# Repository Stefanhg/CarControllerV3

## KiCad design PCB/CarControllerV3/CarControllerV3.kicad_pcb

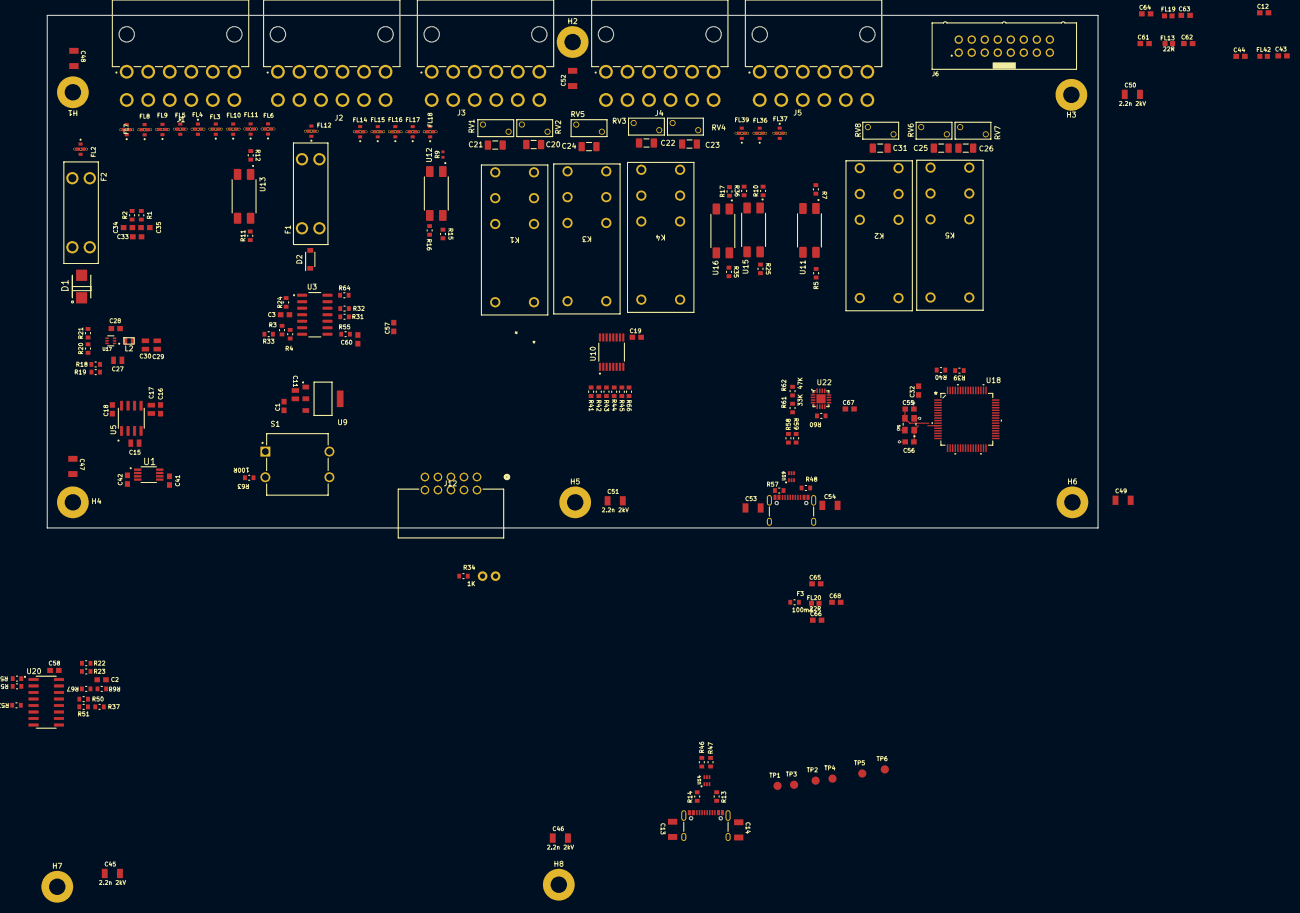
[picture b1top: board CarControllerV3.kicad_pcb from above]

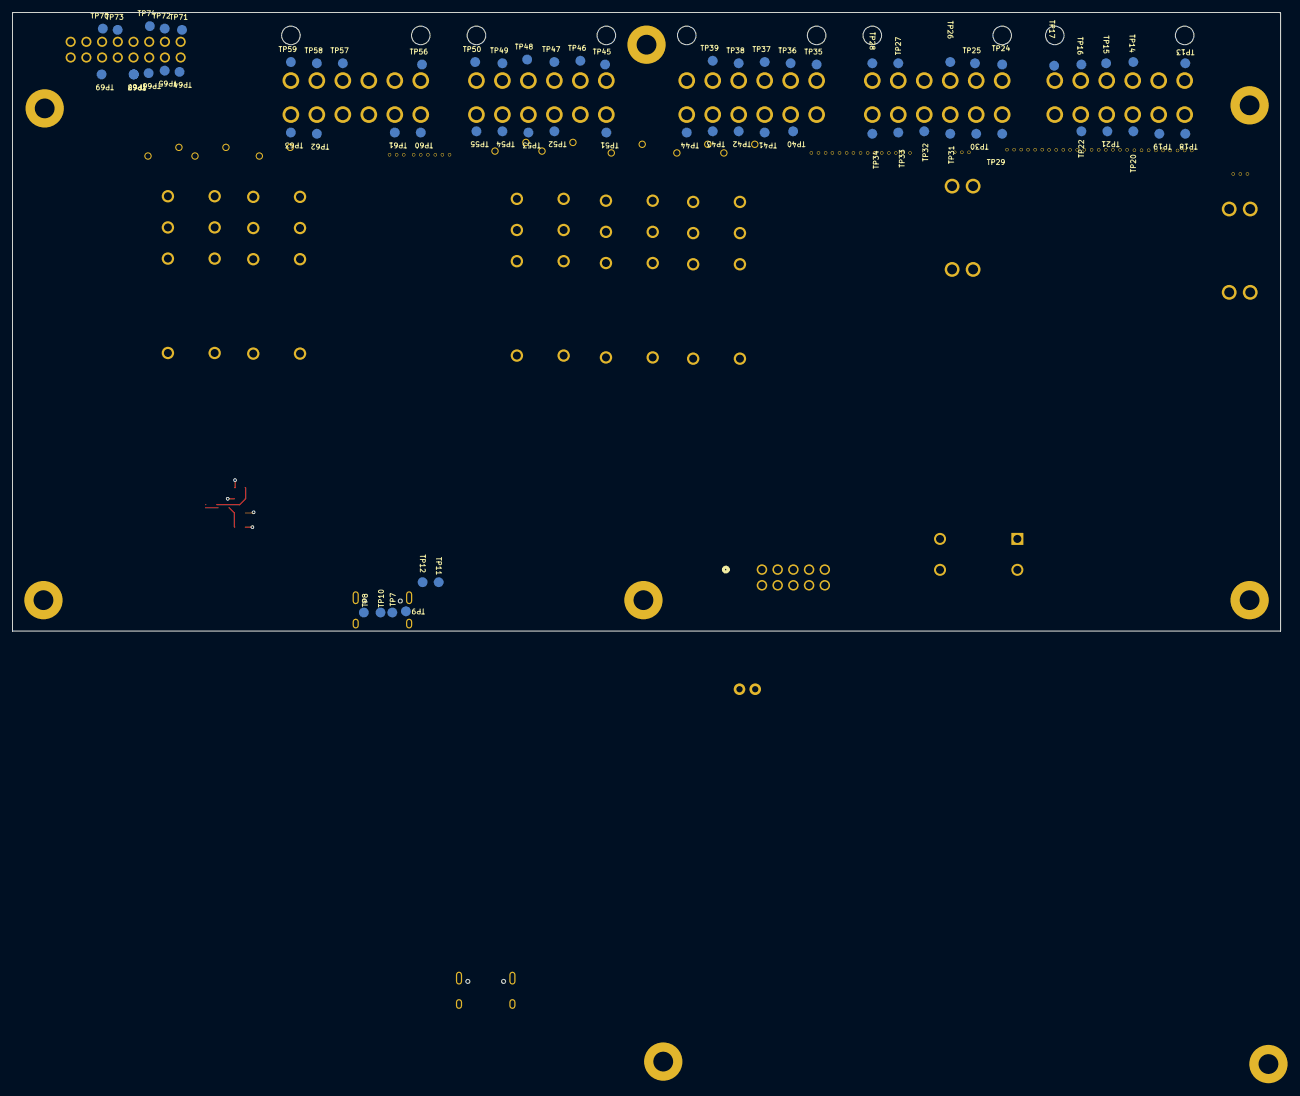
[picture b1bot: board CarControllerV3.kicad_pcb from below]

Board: 2 copper layers, 205.0 x 100.0 mm, 263 parts (67 on the bottom side), 171 nets.

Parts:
C1, C2, C3, C12, C16, C18, C19, C28, C32, C41, C42, C57, C58, C65, C66, C67: 100n; CAPC1608X90
C11, C15, C17, C27, C29, C30: 10uF; CC0805KKX5R8BB106-CAPC2013X145N
C13, C14, C45, C46, C47, C48, C49, C50, C51, C52, C53, C54: 2.2n 2kV; C1206X222KGRACTU-CAP3216X125N
C20, C21, C22, C23, C24, C25, C26, C31: 100n; CAPC3216X180N
C33, C34, C35, C60: 100p; CAPC1608X90
C43, C44, C61, C62, C63, C64: 10n; CAPC1608X90
C55, C56: 12p; CAPC1608X90
C68: 1uF; CAPC1608X90
D1: SS54B; SS54B-DIOM4336X244N
D2: 1N4007W-T; SODFL3818X130N
F1, F2: 3557-2; FUSE_3557-2
F3: 100mA; FEMTOSMDC010F-2-RESC1608X60N
FL2, FL3, FL4, FL5, FL6, FL7, FL8, FL9, FL10, FL11, FL12, FL14, FL15, FL16, FL17, FL18, FL36, FL37, FL39: 22nF; FIL_NFM21CC223R1H3D
FL13, FL19, FL20, FL42: 22R; BLM18BA220SN1D-BEADC1608X95N
H1, H2, H3, H4, H5, H6, H7, H8: 3.2mm; 3.2mm_plated
J1, J2, J3, J4, J5: 649012227222
J6: 61201621621
J9, J11: USB_C_Receptacle; USB-C_16
J10: Conn_01x02; 1x02
J12: 702471052; CONN_7024710XX_MOL
K1, K2, K3, K4, K5: RT424005; RELAY-SPDT_5mm
L2: 4.7uH; CC0805
R1, R2, R3, R4, R5, R11, R23, R25, R31, R32, R33, R35, R60, R67: 10K; RC0603FR-RESC1608X60N
R7, R12: 22K; RC0603FR-RESC1608X60N.pretty
R9: 1K; RC0402FR-RESC1005X40N
R10, R17: 2.7K; RC0603FR-RESC1608X60N.pretty
R13, R14, R48, R57: 5.1K; RC0603FR-RESC1608X60N.pretty
R15, R16, R55, R63, R64: 100R; RC0603FR-RESC1608X60N.pretty
R18, R21: 7.5K; RC0603FR-RESC1608X60N.pretty
R19, R20: 39K; RC0603FR-RESC1608X60N.pretty
R22: 390K; RC0603FR-RESC1608X60N.pretty
R24, R34, R37, R39, R40, R41, R42, R43, R44, R45, R50, R51, R52, R53, R54, R66, R68: 1K; RC0603FR-RESC1608X60N.pretty
R36: N.M.; RC0603FR-RESC1608X60N.pretty
R46, R47, R58, R59: 22R; RC0603FR-RESC1608X60N.pretty
R61: 33K; RC0603FR-RESC1608X60N.pretty
R62: 47K; RC0603FR-RESC1608X60N.pretty
RV1, RV2, RV3, RV4, RV5, RV6, RV7, RV8: 100V 400A; VAR_B72205S0600K101
S1: TS13-1212-73-BK-260-D; SW_TS13-1212-73-BK-260-D
TP1, TP2, TP3, TP4, TP5, TP6, TP7, TP8, TP9, TP10, TP11, TP12, TP13, TP14, TP15, TP16, TP17, TP18, TP19, TP20, TP21, TP22, TP24, TP25, TP26, TP27, TP28, TP29, TP30, TP31, TP32, TP33, TP34, TP35, TP36, TP37, TP38, TP39, TP40, TP41, TP42, TP43, TP44, TP45, TP46, TP47, TP48, TP49, TP50, TP51, TP52, TP53, TP54, TP55, TP56, TP57, TP58, TP59, TP60, TP61, TP62, TP63, TP64, TP65, TP66, TP67, TP68, TP69, TP70, TP71, TP72, TP73, TP74: TP_B1_6; testpoints-B1_6
U1: REF5025AIDGKT; REF5025AIDGKT-SOP65P490X110-8N
U3: OPA4188AIDR; SOIC127P600X175-14N
U5: ICL7660AIBAZA; SOIC127P600X175-8N
U9: AMS1117-3.3; SOT229P700X180-4N
U10: ULN2003APW; SOP65P640X120-16N
U11, U12, U13, U15, U16: PC817X1NIP1B; SOIC254P960X420-4N
U14, U19: USBLC6-2P6; USBLC6-2P6-SOT50P160X60-6N
U17: AP62200Z6-7; SOT50P160X60-6N
U18: STM32C092RCT6; LQFP64_STM
U20: CD4051BM96; SOIC127P600X175-16N
U22: CP2102N-A01-GQFN20R; SILABS_QFN20
Y1: 16MHz; XTAL_ECS-160-12-33Q-JES-TR

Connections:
+3V3: C3.2 (C2), C11.2, C32.1 (C1), C58.1 (C1), R5.1 (R1), R11.1 (R1), R25.2 (R2), R34.1 (R1), R35.2 (R2), R37.1 (R1), R39.1 (R1), R40.1 (R1), U3.4 (V+), U9.2 (VOUT), U14.5 (VBUS), U18.8 (VDD/VDDA), U19.5 (VBUS), U20.16 (VDD)
+5V: C1.1 (C1), C19.1 (C1), C29.2, C30.2, C42.2 (C2), C62.2 (C2), FL13.1 (R1), FL36.1, K1.A1 (+), K2.A1 (+), K3.A1 (+), K4.A1 (+), K5.A1 (+), L2.2, R19.1 (R1), U1.2 (VIN), U9.3 (VIN), U10.9 (COM)
+12V: C18.2 (C2), C27.2, C44.2 (C2), D1.C, FL4.3, FL42.1 (R1), R20.1 (R1), U5.8 (V+), U17.1 (VIN)
+12v_sense: C2.1 (C1), R67.2 (R2), R68.1 (R1), U20.14 (CH1_IN/OUT)
+HV: D2.1 (C), R22.1 (R1)
-12V: C16.2 (C2), C17.2, C64.2 (C2), FL19.1 (R1), U5.5 (VOUT)
ACCELERATOR_SWITCH: R11.2 (R2), U13.4, U18.59 (PB5)
ADC_INPUT: C60.2 (C2), R55.1 (R1)
Buzzer: J6.9, U18.27 (PB0)
CHARGER_STOP_SIG: R25.1 (R1), U15.4, U18.61 (PB7)
DCDC_EN: R9.1 (R1), U18.28 (PB1)
Earth: C19.2 (C2), C45.2 (C2), C46.2 (C2), C47.1 (C1), C48.1 (C1), C49.2 (C2), C50.2 (C2), C51.1 (C1), C52.1 (C1), FL2.2, FL2.2_1, FL2.2_2, FL2.2_3, FL2.2_4, FL3.2, FL3.2_1, FL3.2_2, FL3.2_3, FL3.2_4, FL4.2, FL4.2_1, FL4.2_2, FL4.2_3, FL4.2_4, FL5.2, FL5.2_1, FL5.2_2, FL5.2_3, FL5.2_4, FL6.2, FL6.2_1, FL6.2_2, FL6.2_3, FL6.2_4, FL7.2, FL7.2_1, FL7.2_2, FL7.2_3, FL7.2_4, FL8.2, FL8.2_1, FL8.2_2, FL8.2_3, FL8.2_4, FL9.2, FL9.2_1, FL9.2_2, FL9.2_3, FL9.2_4, FL10.2, FL10.2_1, FL10.2_2, FL10.2_3, FL10.2_4, FL11.2, FL11.2_1, FL11.2_2, FL11.2_3, FL11.2_4, FL12.2, FL12.2_1, FL12.2_2, FL12.2_3, FL12.2_4, FL14.2, FL14.2_1, FL14.2_2, FL14.2_3, FL14.2_4, FL15.2, FL15.2_1, FL15.2_2, FL15.2_3, FL15.2_4, FL16.2, FL16.2_1, FL16.2_2, FL16.2_3, FL16.2_4, FL17.2, FL17.2_1, FL17.2_2, FL17.2_3, FL17.2_4, FL18.2, FL18.2_1, FL18.2_2, FL18.2_3, FL18.2_4, FL36.2, FL36.2_1, FL36.2_2, FL36.2_3, FL36.2_4, FL37.2, FL37.2_1, FL37.2_2, FL37.2_3, FL37.2_4, FL39.2, FL39.2_1, FL39.2_2, FL39.2_3, FL39.2_4
GND: C1.2 (C2), C3.1 (C1), C11.1, C12.2 (C2), C13.1 (C1), C14.1 (C1), C16.1 (C1), C17.1, C18.1 (C1), C27.1, C29.1, C30.1, C32.2 (C2), C34.1 (C1), C35.2 (C2), C41.1 (C1), C42.1 (C1), C43.1 (C1), C44.1 (C1), C53.1 (C1), C54.1 (C1), C55.2 (C2), C56.2 (C2), C57.2 (C2), C58.2 (C2), C60.1 (C1), C61.1 (C1), C62.1 (C1), C63.1 (C1), C64.1 (C1), C65.1 (C1), C66.1 (C1), C67.2 (C2), C68.1 (C1), FL3.3, FL6.3, FL10.1, FL18.1, FL37.3, J6.11, J6.13, J6.15, J9.GND, J11.GND, J12.3, J12.8, R13.2 (R2), R14.2 (R2), R18.2 (R2), R21.2 (R2), R23.2 (R2), R24.2 (R2), R32.2 (R2), R36.1 (R1), R48.2 (R2), R57.2 (R2), R62.2 (R2), R63.2 (R2), R66.2 (R2), TP5.TP, TP11.TP, TP69.TP, U1.4 (GND), U3.11 (V-), U5.3 (GND), U9.1 (GND/ADJ), U10.8 (E), U11.2, U11.3, U12.2, U13.2, U13.3, U14.2 (GND), U15.3, U16.3, U17.3 (GND), U18.9 (VSS/VSSA), U19.2 (GND), U20.7 (VEE), U20.8 (VSS), U22.3 (GND), U22.12 (GND), U22.21 (GND), Y1.2, Y1.4
I2C_ADDR_SEL: J6.4, TP72.TP, U18.29 (PB2)
I2C_ADDR_SEL_2: J6.2, TP71.TP
I2C_SCL: J6.3, R39.2 (R2), TP65.TP, U18.62 (PB8)
I2C_SDA: J6.1, R40.2 (R2), TP64.TP, U18.63 (PB9)
IGNITION_ON: R35.1 (R1), U16.4, U18.60 (PB6)
K1_SIG: R41.2 (R2), U18.31 (PB11)
K2_SIG: R42.2 (R2), U18.32 (PB12)
K3_SIG: R43.2 (R2), U18.33 (PB13)
K4_SIG: R44.2 (R2), U18.34 (PB14)
K5_SIG: R45.2 (R2), U18.35 (PB15)
LDR_Senser: J6.7, R54.2 (R2), TP67.TP, TP68.TP
MCU_RST: J12.1, S1.1, S1.2, U18.12 (PF2-NRST)
NTC: FL9.1, R37.2 (R2), R51.2 (R2)
unnamed: C2.2 (C2), J4.12, R68.2 (R2), TP55.TP
unnamed: C12.1 (C1), C61.2 (C2), FL13.2 (R2), J6.12, J6.14, J6.16, TP70.TP
unnamed: C13.2 (C2), C14.2 (C2), J9.S (SHIELD)
unnamed: C28.1 (C1), L2.1, U17.2 (SW)
unnamed: C28.2 (C2), U17.4 (BST)
unnamed: C33.1 (C1), C34.2 (C2), R2.1 (R1), R4.1 (R1), U3.6 (-IN)
unnamed: C33.2 (C2), C35.1 (C1), R1.1 (R1), R3.2 (R2), U3.5 (+IN)
unnamed: C43.2 (C2), FL42.2 (R2), J6.6, TP74.TP
unnamed: C45.1 (C1), H7.1
unnamed: C46.1 (C1), H8.1
unnamed: C47.2 (C2), H4.1
unnamed: C48.2 (C2), H1.1
unnamed: C49.1 (C1), H6.1
unnamed: C50.1 (C1), H3.1
unnamed: C51.2 (C2), H5.1
unnamed: C52.2 (C2), H2.1
unnamed: C53.2 (C2), C54.2 (C2), J11.S (SHIELD)
unnamed: C55.1 (C1), U18.10 (PF0-OSC_IN), Y1.3
unnamed: C56.1 (C1), U18.11 (PF1-OSC_OUT), Y1.1
unnamed: C63.2 (C2), FL19.2 (R2), J6.10, TP73.TP
unnamed: C65.2 (C2), C68.2 (C2), FL20.1 (R1), R61.1 (R1), U22.7 (VREGIN)
unnamed: C66.2 (C2), F3.2, FL20.2 (R2)
unnamed: C67.1 (C1), R60.2 (R2), U22.6 (VDD)
unnamed: D1.A, F2.2_1, F2.2_2
unnamed: D2.2 (A), F1.1_1, F1.1_2
unnamed: F1.2_1, F1.2_2, FL12.1
unnamed: F2.1_1, F2.1_2, FL2.3
unnamed: FL2.1, J1.1, TP13.TP
unnamed: FL3.1, J1.3, TP14.TP
unnamed: FL4.1, J1.4, TP15.TP
unnamed: FL5.1, J1.5, TP16.TP
unnamed: FL6.1, J1.6, TP17.TP
unnamed: FL7.3, J1.7, TP18.TP
unnamed: FL8.3, J1.8, TP19.TP
unnamed: FL9.3, J1.9, TP20.TP
unnamed: FL10.3, J1.10, TP21.TP
unnamed: FL11.3, J1.11, TP22.TP
unnamed: FL12.3, J2.12, TP34.TP
unnamed: FL14.3, J3.1, TP35.TP
unnamed: FL15.3, J3.2, TP36.TP
unnamed: FL16.3, J3.3, TP37.TP
unnamed: FL17.3, J3.4, TP38.TP
unnamed: FL18.3, J3.5, J3.7, TP39.TP
unnamed: FL36.3, J5.7, TP60.TP
unnamed: FL37.1, J5.8, TP61.TP
unnamed: FL39.3, J5.1, TP56.TP
unnamed: J2.1, TP24.TP
unnamed: J2.2, TP25.TP
unnamed: J2.3, TP26.TP
unnamed: J2.5, TP27.TP
unnamed: J2.6, TP28.TP
unnamed: J2.7, TP29.TP
unnamed: J2.8, TP30.TP
unnamed: J2.9, TP31.TP
unnamed: J2.10, TP32.TP
unnamed: J2.11, TP33.TP
unnamed: J9.A5 (CC1), R14.1 (R1), TP1.TP
unnamed: J9.B5 (CC2), R13.1 (R1), TP2.TP
unnamed: J10.1, R34.2 (R2)
unnamed: J11.A5 (CC1), R57.1 (R1), TP7.TP
unnamed: J11.B5 (CC2), R48.1 (R1), TP8.TP
unnamed: C20.2, C21.2, J3.10, K1.11 (COM), K1.21 (COM), RV1.2, RV2.2, TP42.TP
unnamed: C20.1, J3.12, K1.12 (NC), K1.22 (NC), RV2.1, TP44.TP
unnamed: C21.1, J3.11, K1.14 (NO), K1.24 (NO), RV1.1, TP43.TP
unnamed: K1.A2 (-), U10.16 (1C)
unnamed: C31.2, J5.11, K2.11 (COM), K2.21 (COM), RV8.2, TP62.TP
unnamed: C31.1, J5.12, K2.12 (NC), K2.22 (NC), RV8.1, TP63.TP
unnamed: K2.14 (NO), K2.24 (NO)
unnamed: K2.A2 (-), U10.15 (2C)
unnamed: C24.1, J4.2, K3.11 (COM), K3.21 (COM), RV5.1, TP46.TP
unnamed: C24.2, J4.1, K3.12 (NC), K3.22 (NC), RV5.2, TP45.TP
unnamed: K3.A2 (-), U10.14 (3C)
unnamed: C22.2, C23.2, J4.3, K4.11 (COM), K4.21 (COM), RV3.2, RV4.2, TP47.TP
unnamed: C23.1, J4.5, K4.12 (NC), K4.22 (NC), RV4.1, TP49.TP
unnamed: C22.1, J4.4, K4.14 (NO), K4.24 (NO), RV3.1, TP48.TP
unnamed: K4.A2 (-), U10.13 (4C)
unnamed: C25.2, C26.2, J5.4, K5.11 (COM), K5.21 (COM), RV6.2, RV7.2, TP57.TP
unnamed: C26.1, J5.6, K5.12 (NC), K5.22 (NC), RV7.1, TP59.TP
unnamed: C25.1, J5.5, K5.14 (NO), K5.24 (NO), RV6.1, TP58.TP
unnamed: K5.A2 (-), U10.12 (5C)
unnamed: R3.1 (R1), R33.2 (R2), U3.7 (OUT)
unnamed: J4.6, R7.1 (R1), TP50.TP
unnamed: R7.2 (R2), U11.1
unnamed: R9.2 (R2), U12.1
unnamed: R10.1 (R1), U15.1
unnamed: J4.7, R10.2 (R2), TP51.TP
unnamed: FL11.1, R12.1 (R1)
unnamed: R12.2 (R2), U13.1
unnamed: R15.1 (R1), U12.4
unnamed: J3.8, R15.2 (R2), TP40.TP
unnamed: R16.1 (R1), U12.3
unnamed: J3.9, R16.2 (R2), TP41.TP
unnamed: R17.1 (R1), U16.1
unnamed: J4.9, R17.2 (R2), TP52.TP
unnamed: R18.1 (R1), R19.2 (R2), U17.6 (FB)
unnamed: R20.2 (R2), R21.1 (R1), U17.5 (EN)
unnamed: R22.2 (R2), R23.1 (R1), U20.15 (CH2_IN/OUT)
unnamed: R24.1 (R1), U3.3 (+IN)
unnamed: R31.2 (R2), R32.1 (R1), U3.12 (+IN)
unnamed: J4.10, R36.2 (R2), TP53.TP, U15.2, U16.2
unnamed: R41.1 (R1), U10.1 (1B)
unnamed: R42.1 (R1), U10.2 (2B)
unnamed: R43.1 (R1), U10.3 (3B)
unnamed: R44.1 (R1), U10.4 (4B)
unnamed: R45.1 (R1), U10.5 (5B)
unnamed: R46.2 (R2), U14.6 (I/O1_2)
unnamed: R47.2 (R2), U14.4 (I/O2_2)
unnamed: R50.1 (R1), U20.13 (CH0_IN/OUT)
unnamed: R51.1 (R1), U20.12 (CH3_IN/OUT)
unnamed: R52.1 (R1), U20.1 (CH4_IN/OUT)
unnamed: R53.1 (R1), U20.5 (CH5_IN/OUT)
unnamed: R54.1 (R1), U20.2 (CH6_IN/OUT)
unnamed: R55.2 (R2), U3.8 (OUT), U3.9 (-IN)
unnamed: R58.2 (R2), U19.6 (I/O1_2)
unnamed: R59.2 (R2), U19.4 (I/O2_2)
unnamed: R60.1 (R1), U22.9 (RST)
unnamed: R61.2 (R2), R62.1 (R1), U22.8 (VBUS)
unnamed: R63.1 (R1), S1.3, S1.4
unnamed: R64.2 (R2), U3.13 (-IN), U3.14 (OUT)
unnamed: R66.1 (R1), U10.6 (6B), U10.7 (7B)
unnamed: J4.11, R67.1 (R1), TP54.TP
unnamed: U1.1 (DNC), U1.8 (DNC)
unnamed: U3.1 (OUT), U3.2 (-IN)
unnamed: C15.1, U5.2 (CAP+)
unnamed: C15.2, U5.4 (CAP-)
unnamed: J9.A6 (D+), J9.B6 (D+), TP3.TP, U14.1 (I/O1_1)
unnamed: J9.A7 (D-), J9.B7 (D-), TP4.TP, U14.3 (I/O2_1)
unnamed: J11.A6 (D+), J11.B6 (D+), TP9.TP, U19.1 (I/O1_1)
unnamed: J11.A7 (D-), J11.B7 (D-), TP10.TP, U19.3 (I/O2_1)
unnamed: U3.10 (+IN), U20.3 (COM_OUT/IN)
REV_SIG: R5.2 (R2), U11.4, U18.58 (PB4)
SHUNT_ANA: R33.1 (R1), R52.2 (R2)
SPEEDMODE_ANA: FL39.1, R53.2 (R2)
SWDCLK_BOOT0: J10.2, J12.6, U18.46 (PA14-BOOT0)
SWDIO: J12.7, U18.45 (PA13)
Shunt+: FL7.1, FL14.1, R2.2 (R2)
Shunt-: FL8.1, FL15.1, R1.2 (R2)
UART_RX: U18.25 (PC4), U22.17 (RXD)
UART_TX: U18.26 (PC5), U22.18 (TXD)
USB_d+: R46.1 (R1), R58.1 (R1), U22.4 (D+)
USB_d-: R47.1 (R1), R59.1 (R1), U22.5 (D-)
VBUS: F3.1, J9.VBUS, J11.VBUS, TP6.TP, TP12.TP
VREF: C41.2 (C2), C57.1 (C1), R31.1 (R1), U1.6 (VOUT), U18.7 (VREF+)
VREF/2: R4.2 (R2), R50.2 (R2), R64.1 (R1)
trip_button: J6.5, TP66.TP, U18.57 (PB3)
